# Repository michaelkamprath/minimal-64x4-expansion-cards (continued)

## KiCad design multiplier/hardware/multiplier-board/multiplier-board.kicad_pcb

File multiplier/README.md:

# Integer Multiplication Accelerator for the Minimal 64x4 Computer
This project enables hardware-accelerated multiplication on the [Minimal 64x4 Home Computer](https://github.com/slu4coder/Minimal-64x4-Home-Computer/), exploring how multiplication works at a fundamental level in both software and hardware, using the Minimal 64x4 homebrew computer as a real-world test platform. Starting with a classic shifted-add multiplication algorithm implemented entirely in assembly, the project demonstrates both the mechanics and performance limits of software-based multiplication on an 8-bit CPU.

To dramatically improve performance, a dedicated hardware multiplier card is designed and built using discrete 74-series logic. The board implements a fully combinational 8-bit × 8-bit multiplier with memory-mapped I/O, allowing the CPU to offload multiplication and receive a 16-bit result in just a few clock cycles. The design is then extended in software to support full 16-bit × 16-bit multiplication through careful carry management.

The impact of hardware acceleration is demonstrated using a Mandelbrot renderer, where thousands of multiplications per frame make performance differences immediately visible. By comparing software-only and hardware-accelerated runs on real hardware, the project shows how a simple, purpose-built coprocessor can transform computational performance on a retro-style system.

# Hardware Multiplier Design
The hardware multiplier is a memory-mapped expansion board for the Minimal 64x4 that implements an 8-bit × 8-bit unsigned multiplication entirely in combinational logic. The design uses a planar array of 74AHCT08 AND gates to generate all partial products, followed by a cascade of 74HCT283 4-bit adders to sum those partial products and propagate carries. Because the multiplier core is purely combinational, no clocking, state machine, or control logic is required; once valid operands are presented, the result settles after the inherent gate propagation delay.

Operands are latched from the system data bus using 74AHCT374 registers to isolate the combinational logic from the shared bus and to ensure stable inputs during computation. The 16-bit result is continuously driven internally and presented to the host system through 74AHCT245 bidirectional bus transceivers when the board is selected. Address decoding is handled using 74HCT688 magnitude comparators, with a small programmable logic device (ATF16V8) providing glue logic for timing, output enable control, and bus arbitration.

Worst-case propagation delay is dominated by carry propagation through the adder array and is approximately 160 ns, corresponding to roughly two CPU cycles on an 8 MHz Minimal 64x4. From the CPU’s perspective, multiplication is reduced to a small number of memory writes and reads, enabling a substantial performance improvement over the software-only shifted-add implementation.

```text
                     ┌─────────────────────────┐
                     │        CPU / BUS        │
                     │  Address • Data • Ctrl  │
                     └───────────┬─────────────┘
                                 │
                        Memory-Mapped I/O
                                 │
        ┌────────────────────────▼────────────────────────┐
        │            Hardware Multiplier Board            │
        │                                                 │
        │  ┌───────────────┐      ┌────────────────────┐  │
        │  │ Input Latch A │◄─────┤                    │  │
        │  │  (8-bit)      │      │                    │  │
        │  └───────────────┘      │                    │  │
        │                         │                    │  │
        │  ┌───────────────┐      │  Combinational     │  │
        │  │ Input Latch B │◄─────┤  Multiplier Core   │  │
        │  │  (8-bit)      │      │  (AND Plane +      │  │
        │  └───────────────┘      │   Adder Array)     │  │
        │                         │                    │  │
        │                         │                    │  │
        │                         └─────────┬──────────┘  │
        │                                   │             │
        │                          16-bit Result          │
        │                                   │             │
        │                    ┌──────────────▼────────────┐│
        │                    │  Output Bus Transceivers  ││
        │                    │       (16-bit)            ││
        │                    └──────────────┬────────────┘│
        │                                   │             │
        │  ┌──────────────────────────┐     │             │
        │  │ Address Decode & Control │◄────┘             │
        │  │ (Comparators + PLD)      │                   │
        │  └──────────────────────────┘                   │
        └─────────────────────────────────────────────────┘
```
The overall structure of the hardware multiplier is shown in the block diagram above. The board interfaces with the CPU exclusively through memory-mapped I/O on the shared system bus. Operand values are written by the CPU into two 8-bit input latches (Operand A and Operand B), which isolate the multiplier core from bus activity and continuously present stable inputs to the combinational logic.

At the center of the design is a purely combinational multiplier core composed of an AND-gate partial-product plane followed by an adder array that collapses those partial products into a 16-bit result. Because the core has no internal state, clocking, or control signals, the result is produced automatically as signals propagate through the logic once the operands are latched.

The 16-bit result is connected to the system data bus through output bus transceivers that are enabled only during valid read cycles. Address decoding and timing control logic ensure the board responds only within its assigned address range and never drives the bus outside of those cycles. From the CPU’s perspective, the hardware multiplier appears as a small set of deterministic, memory-mapped registers, with computation latency bounded solely by combinational propagation delay.

# Compiling the Software
All software found in the [software](./software/) directory is compiled with [BespokeASM](https://github.com/michaelkamprath/bespokeasm), which supports the Minimal 64x4. [Carsten Herting](https://github.com/slu4coder), the creator of the Minimal 64x4, also provides an assembler for it, but that assembler is quite minimal (by design). One key shortcoming is the inability to import library code into the current compilation. BespokeASM enables importing libraries and includes several other features that this project’s software depends on.

To compile the speech code in this repository, use the following command:

```sh
bespokeasm compile -c /path/to/bespokeasm/examples/slu4-minimal-64x4/slu4-minimal-64x4.yaml -n -p -t intel_hex -D USE_ACCELERATOR mandelbrot.min64x4
```
Where `/path/to/bespokeasm` is the path to the BespokeASM repository on your computer. You may remove the `-D USE_ACCELERATOR` if you wish to compile the program to use software-only multiplication.

This will produce an Intel HEX representation of the compiled program, which can then be sent to the Minimal 64x4 using its `receive` command.

# Video

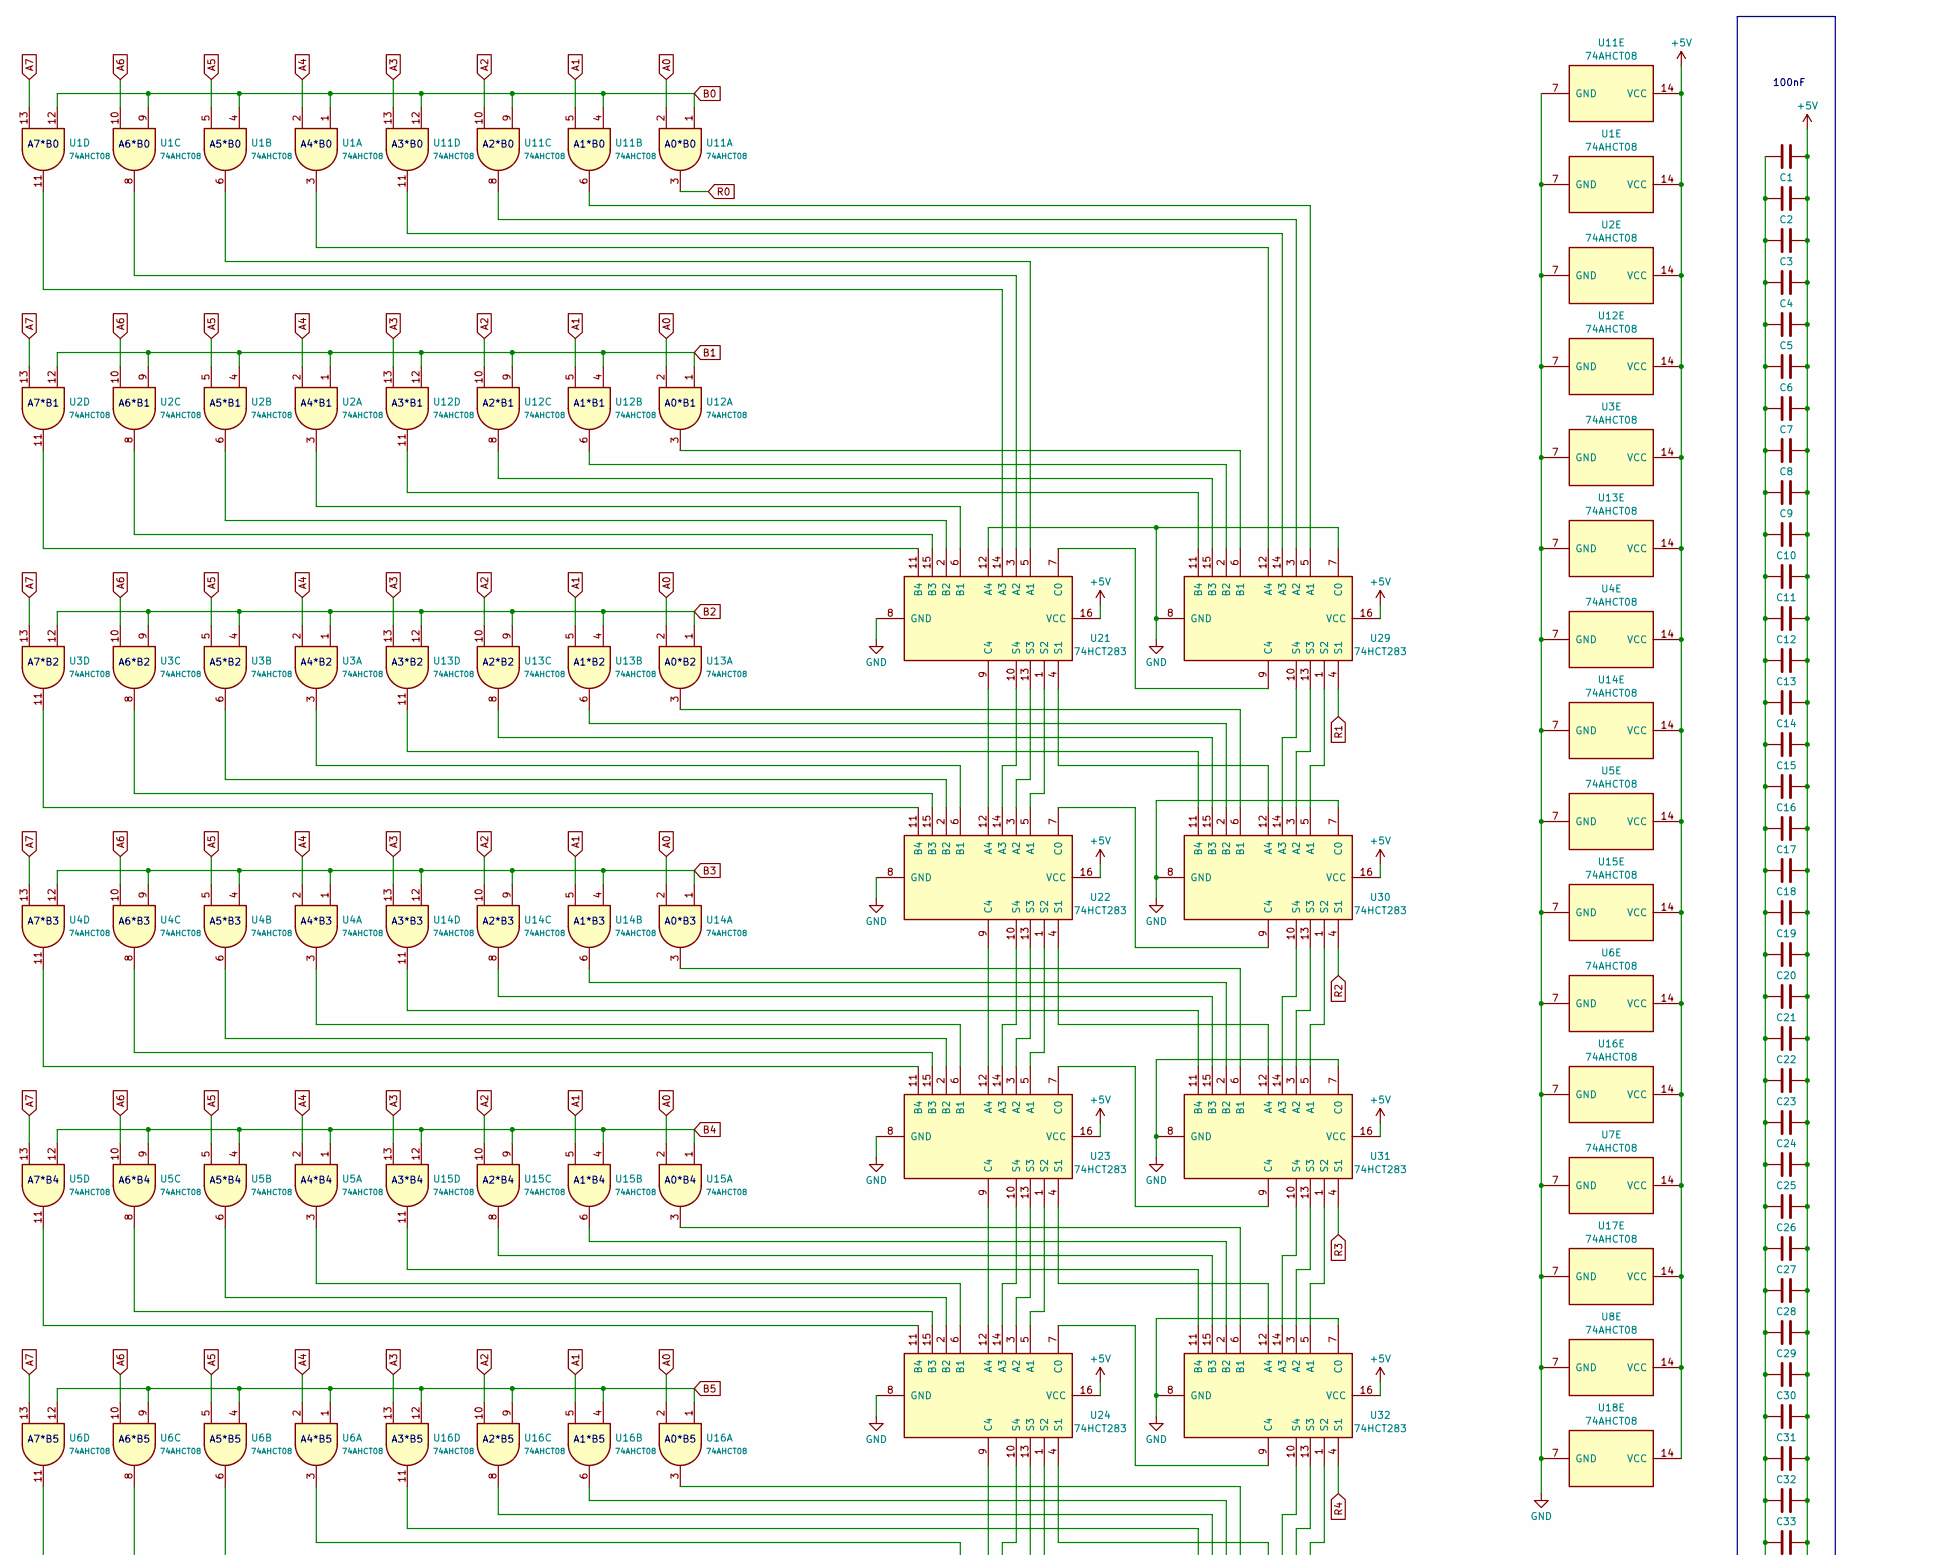
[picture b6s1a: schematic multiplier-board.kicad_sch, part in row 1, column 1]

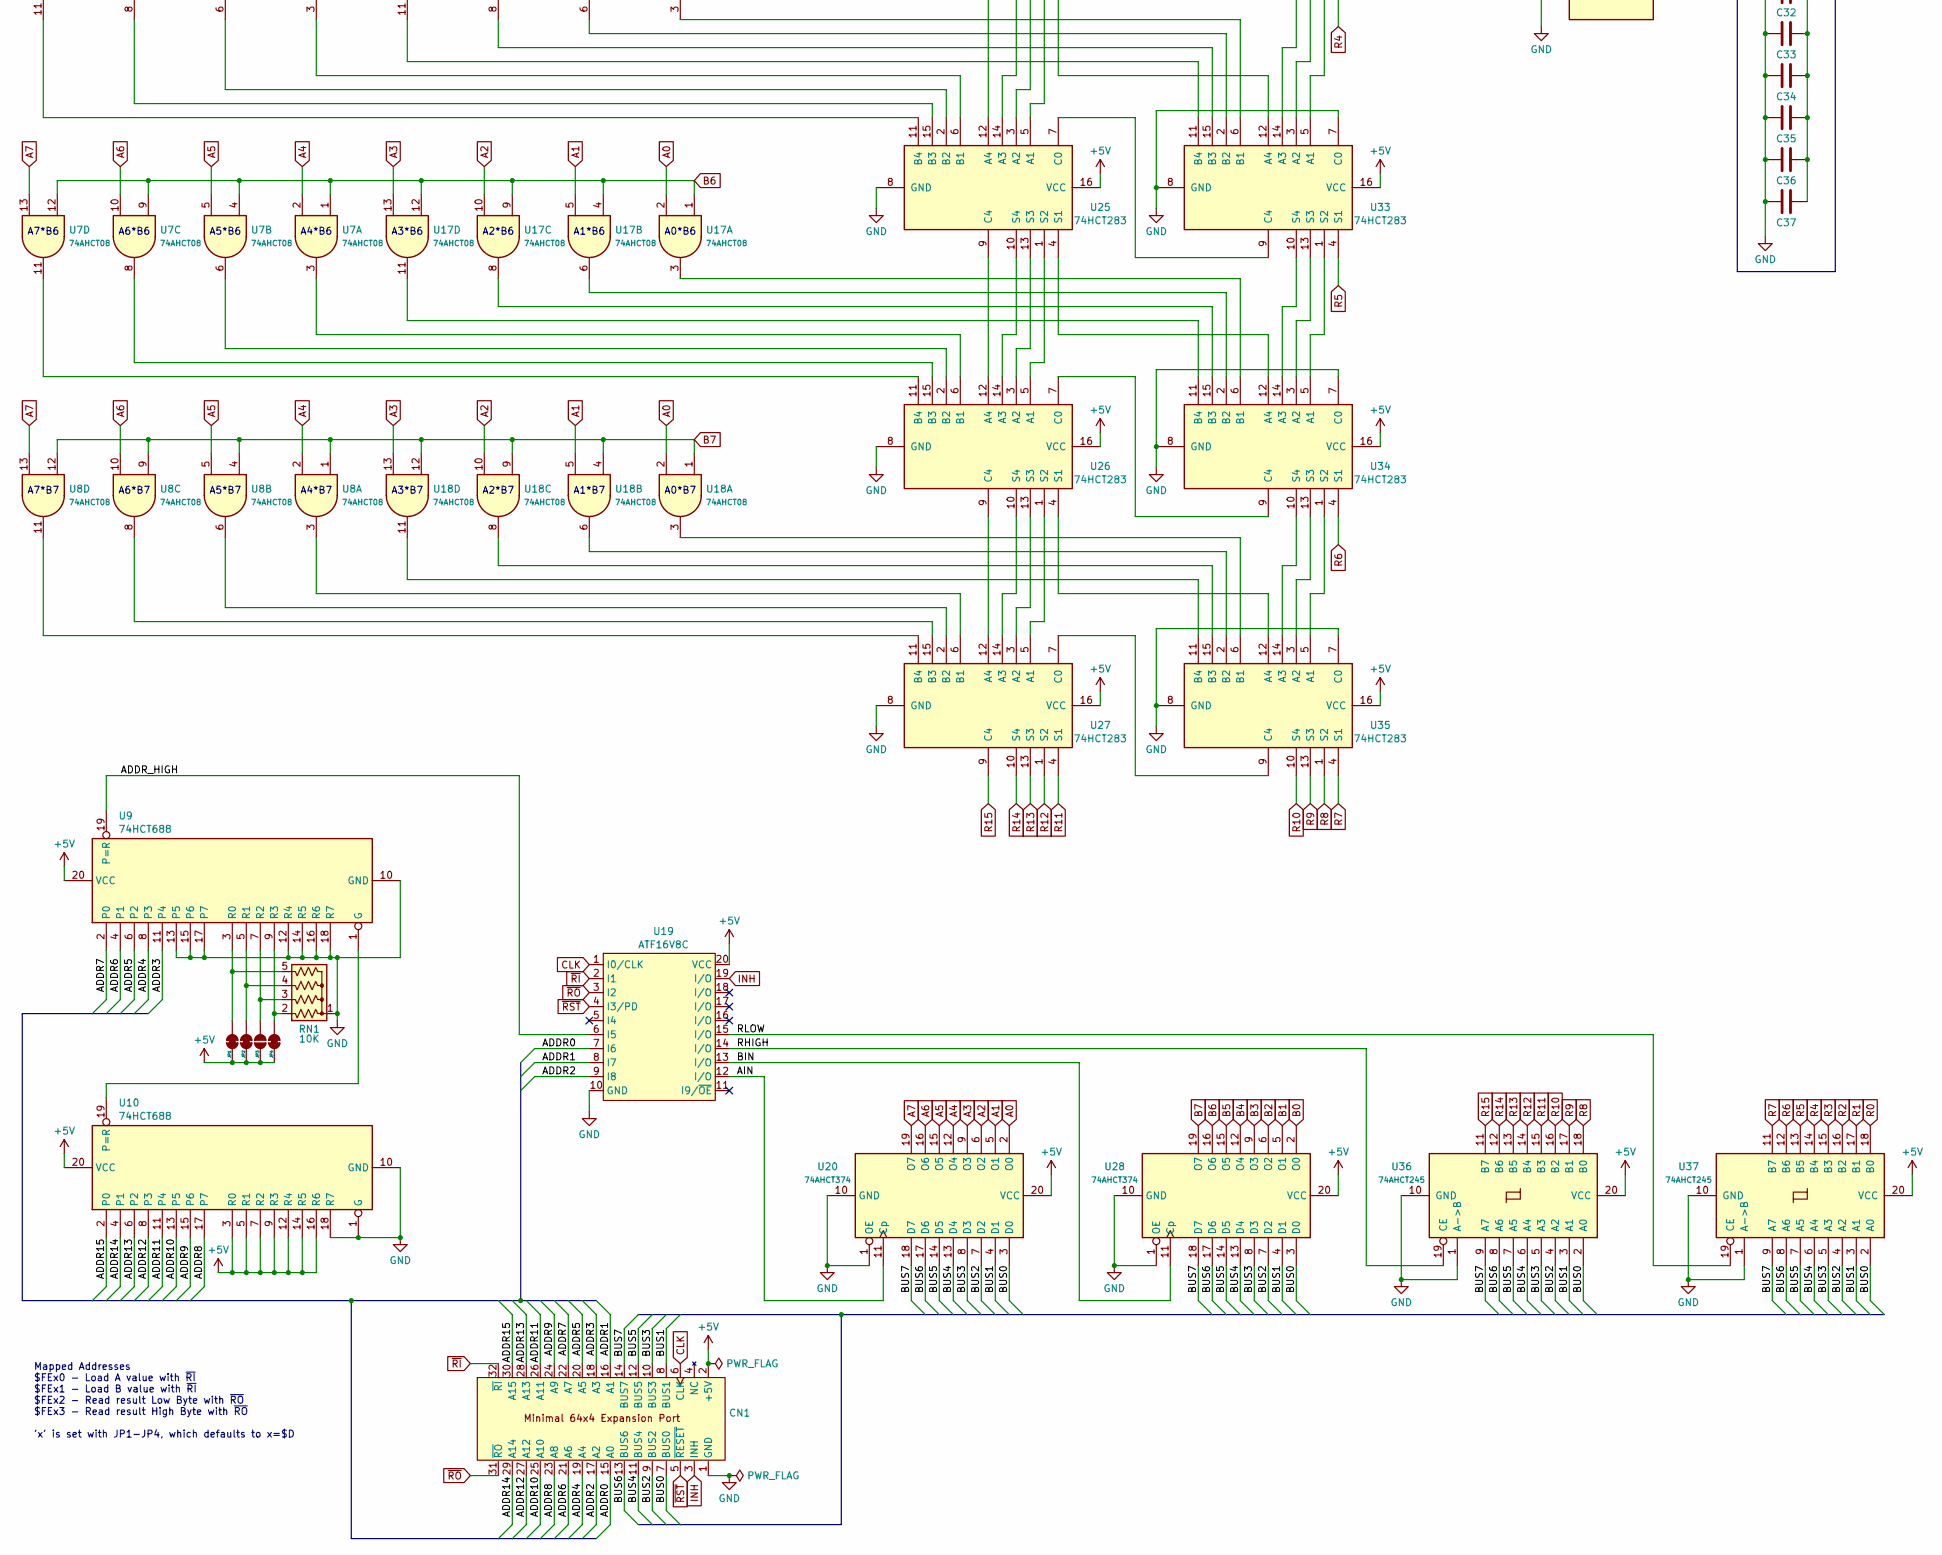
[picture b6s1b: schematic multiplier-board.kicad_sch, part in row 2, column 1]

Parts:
C1, C2, C3, C4, C5, C6, C7, C8, C9, C10, C11, C12, C13, C14, C15, C16, C17, C18, C19, C20, C21, C22, C23, C24, C25, C26, C27, C28, C29, C30, C31, C32, C33, C34, C35, C36, C37: 100 nF; C_0805_2012Metric_Pad1.18x1.45mm_HandSolder
CN1: PinHeader_2x16_P2.54mm_Horizontal
JP1, JP2, JP4: SolderJumper_2_Bridged; SolderJumper-2_P1.3mm_Bridged_RoundedPad1.0x1.5mm
JP3: SolderJumper_2_Open; SolderJumper-2_P1.3mm_Open_RoundedPad1.0x1.5mm
RN1: 10K; R_Array_SIP5
U1, U2, U3, U4, U5, U6, U7, U8, U11, U12, U13, U14, U15, U16, U17, U18: 74AHCT08; SOIC-14_3.9x8.7mm_P1.27mm
U9, U10: 74HCT688; SOIC-20W_7.5x12.8mm_P1.27mm
U19: ATF16V8C; DIP-20_W7.62mm_Socket
U20, U28: 74AHCT374; SOIC-20W_7.5x12.8mm_P1.27mm
U21, U22, U23, U24, U25, U26, U27, U29, U30, U31, U32, U33, U34, U35: 74HCT283; SOIC-16_3.9x9.9mm_P1.27mm
U36, U37: 74AHCT245; SOIC-20W_7.5x12.8mm_P1.27mm

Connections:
+5V: C1.2, C2.2, C3.2, C4.2, C5.2, C6.2, C7.2, C8.2, C9.2, C10.2, C11.2, C12.2, C13.2, C14.2, C15.2, C16.2, C17.2, C18.2, C19.2, C20.2, C21.2, C22.2, C23.2, C24.2, C25.2, C26.2, C27.2, C28.2, C29.2, C30.2, C31.2, C32.2, C33.2, C34.2, C35.2, C36.2, C37.2, CN1.2 (+5V), JP1.1 (A), JP2.1 (A), JP3.1 (A), JP4.1 (A), U1.14 (VCC), U2.14 (VCC), U3.14 (VCC), U4.14 (VCC), U5.14 (VCC), U6.14 (VCC), U7.14 (VCC), U8.14 (VCC), U9.20 (VCC), U10.3 (R0), U10.5 (R1), U10.7 (R2), U10.9 (R3), U10.12 (R4), U10.14 (R5), U10.16 (R6), U10.20 (VCC), U11.14 (VCC), U12.14 (VCC), U13.14 (VCC), U14.14 (VCC), U15.14 (VCC), U16.14 (VCC), U17.14 (VCC), U18.14 (VCC), U19.20 (VCC), U20.20 (VCC), U21.16 (VCC), U22.16 (VCC), U23.16 (VCC), U24.16 (VCC), U25.16 (VCC), U26.16 (VCC), U27.16 (VCC), U28.20 (VCC), U29.16 (VCC), U30.16 (VCC), U31.16 (VCC), U32.16 (VCC), U33.16 (VCC), U34.16 (VCC), U35.16 (VCC), U36.20 (VCC), U37.20 (VCC)
/ADDR0: CN1.15 (A0), U19.7 (I6)
/ADDR1: CN1.16 (A1), U19.8 (I7)
/ADDR2: CN1.17 (A2), U19.9 (I8)
/ADDR3: CN1.18 (A3), U9.11 (P4)
/ADDR4: CN1.19 (A4), U9.8 (P3)
/ADDR5: CN1.20 (A5), U9.6 (P2)
/ADDR6: CN1.21 (A6), U9.4 (P1)
/ADDR7: CN1.22 (A7), U9.2 (P0)
/ADDR8: CN1.23 (A8), U10.17 (P7)
/ADDR9: CN1.24 (A9), U10.15 (P6)
/ADDR10: CN1.25 (A10), U10.13 (P5)
/ADDR11: CN1.26 (A11), U10.11 (P4)
/ADDR12: CN1.27 (A12), U10.8 (P3)
/ADDR13: CN1.28 (A13), U10.6 (P2)
/ADDR14: CN1.29 (A14), U10.4 (P1)
/ADDR15: CN1.30 (A15), U10.2 (P0)
/ADDR_HIGH: U9.19 (P=R), U19.6 (I5)
/AIN: U19.12 (I/O), U20.11 (Cp)
/BIN: U19.13 (I/O), U28.11 (Cp)
/BUS0: CN1.7 (BUS0), U20.3 (D0), U28.3 (D0), U36.2 (A0), U37.2 (A0)
/BUS1: CN1.8 (BUS1), U20.4 (D1), U28.4 (D1), U36.3 (A1), U37.3 (A1)
/BUS2: CN1.9 (BUS2), U20.7 (D2), U28.7 (D2), U36.4 (A2), U37.4 (A2)
/BUS3: CN1.10 (BUS3), U20.8 (D3), U28.8 (D3), U36.5 (A3), U37.5 (A3)
/BUS4: CN1.11 (BUS4), U20.13 (D4), U28.13 (D4), U36.6 (A4), U37.6 (A4)
/BUS5: CN1.12 (BUS5), U20.14 (D5), U28.14 (D5), U36.7 (A5), U37.7 (A5)
/BUS6: CN1.13 (BUS6), U20.17 (D6), U28.17 (D6), U36.8 (A6), U37.8 (A6)
/BUS7: CN1.14 (BUS7), U20.18 (D7), U28.18 (D7), U36.9 (A7), U37.9 (A7)
/RHIGH: U19.14 (I/O), U36.19 (CE)
/RLOW: U19.15 (I/O), U37.19 (CE)
A0: U11.2, U12.2, U13.2, U14.2, U15.2, U16.2, U17.2, U18.2, U20.2 (O0)
A1: U11.5, U12.5, U13.5, U14.5, U15.5, U16.5, U17.5, U18.5, U20.5 (O1)
A2: U11.10, U12.10, U13.10, U14.10, U15.10, U16.10, U17.10, U18.10, U20.6 (O2)
A3: U11.13, U12.13, U13.13, U14.13, U15.13, U16.13, U17.13, U18.13, U20.9 (O3)
A4: U1.2, U2.2, U3.2, U4.2, U5.2, U6.2, U7.2, U8.2, U20.12 (O4)
A5: U1.5, U2.5, U3.5, U4.5, U5.5, U6.5, U7.5, U8.5, U20.15 (O5)
A6: U1.10, U2.10, U3.10, U4.10, U5.10, U6.10, U7.10, U8.10, U20.16 (O6)
A7: U1.13, U2.13, U3.13, U4.13, U5.13, U6.13, U7.13, U8.13, U20.19 (O7)
B0: U1.1, U1.4, U1.9, U1.12, U11.1, U11.4, U11.9, U11.12, U28.2 (O0)
B1: U2.1, U2.4, U2.9, U2.12, U12.1, U12.4, U12.9, U12.12, U28.5 (O1)
B2: U3.1, U3.4, U3.9, U3.12, U13.1, U13.4, U13.9, U13.12, U28.6 (O2)
B3: U4.1, U4.4, U4.9, U4.12, U14.1, U14.4, U14.9, U14.12, U28.9 (O3)
B4: U5.1, U5.4, U5.9, U5.12, U15.1, U15.4, U15.9, U15.12, U28.12 (O4)
B5: U6.1, U6.4, U6.9, U6.12, U16.1, U16.4, U16.9, U16.12, U28.15 (O5)
B6: U7.1, U7.4, U7.9, U7.12, U17.1, U17.4, U17.9, U17.12, U28.16 (O6)
B7: U8.1, U8.4, U8.9, U8.12, U18.1, U18.4, U18.9, U18.12, U28.19 (O7)
CLK: CN1.6 (CLK), U19.1 (I0/CLK)
GND: C1.1, C2.1, C3.1, C4.1, C5.1, C6.1, C7.1, C8.1, C9.1, C10.1, C11.1, C12.1, C13.1, C14.1, C15.1, C16.1, C17.1, C18.1, C19.1, C20.1, C21.1, C22.1, C23.1, C24.1, C25.1, C26.1, C27.1, C28.1, C29.1, C30.1, C31.1, C32.1, C33.1, C34.1, C35.1, C36.1, C37.1, CN1.1 (GND), RN1.1 (common), U1.7 (GND), U2.7 (GND), U3.7 (GND), U4.7 (GND), U5.7 (GND), U6.7 (GND), U7.7 (GND), U8.7 (GND), U9.10 (GND), U9.12 (R4), U9.13 (P5), U9.14 (R5), U9.15 (P6), U9.16 (R6), U9.17 (P7), U9.18 (R7), U10.1 (G), U10.10 (GND), U10.18 (R7), U11.7 (GND), U12.7 (GND), U13.7 (GND), U14.7 (GND), U15.7 (GND), U16.7 (GND), U17.7 (GND), U18.7 (GND), U19.10 (GND), U20.1 (OE), U20.10 (GND), U21.8 (GND), U21.12 (A4), U22.8 (GND), U23.8 (GND), U24.8 (GND), U25.8 (GND), U26.8 (GND), U27.8 (GND), U28.1 (OE), U28.10 (GND), U29.7 (C0), U29.8 (GND), U30.7 (C0), U30.8 (GND), U31.7 (C0), U31.8 (GND), U32.7 (C0), U32.8 (GND), U33.7 (C0), U33.8 (GND), U34.7 (C0), U34.8 (GND), U35.7 (C0), U35.8 (GND), U36.1 (A->B), U36.10 (GND), U37.1 (A->B), U37.10 (GND)
INH: CN1.3 (INH), U19.19 (I/O)
unnamed: JP1.2 (B), RN1.5 (R4), U9.3 (R0)
unnamed: JP2.2 (B), RN1.4 (R3), U9.5 (R1)
unnamed: JP3.2 (B), RN1.3 (R2), U9.7 (R2)
unnamed: JP4.2 (B), RN1.2 (R1), U9.9 (R3)
unnamed: U9.1 (G), U10.19 (P=R)
unnamed: U1.6, U21.5 (A1)
unnamed: U1.8, U21.3 (A2)
unnamed: U1.11, U21.14 (A3)
unnamed: U2.3, U21.6 (B1)
unnamed: U2.6, U21.2 (B2)
unnamed: U2.8, U21.15 (B3)
unnamed: U2.11, U21.11 (B4)
unnamed: U21.7 (C0), U29.9 (C4)
unnamed: U21.9 (C4), U22.12 (A4)
unnamed: U21.4 (S1), U30.12 (A4)
unnamed: U21.1 (S2), U22.5 (A1)
unnamed: U21.13 (S3), U22.3 (A2)
unnamed: U21.10 (S4), U22.14 (A3)
unnamed: U3.3, U22.6 (B1)
unnamed: U3.6, U22.2 (B2)
unnamed: U3.8, U22.15 (B3)
unnamed: U3.11, U22.11 (B4)
unnamed: U22.7 (C0), U30.9 (C4)
unnamed: U22.9 (C4), U23.12 (A4)
unnamed: U22.4 (S1), U31.12 (A4)
unnamed: U22.1 (S2), U23.5 (A1)
unnamed: U22.13 (S3), U23.3 (A2)
unnamed: U22.10 (S4), U23.14 (A3)
unnamed: U4.3, U23.6 (B1)
unnamed: U4.6, U23.2 (B2)
unnamed: U4.8, U23.15 (B3)
unnamed: U4.11, U23.11 (B4)
unnamed: U23.7 (C0), U31.9 (C4)
unnamed: U23.9 (C4), U24.12 (A4)
unnamed: U23.4 (S1), U32.12 (A4)
unnamed: U23.1 (S2), U24.5 (A1)
unnamed: U23.13 (S3), U24.3 (A2)
unnamed: U23.10 (S4), U24.14 (A3)
unnamed: U5.3, U24.6 (B1)
unnamed: U5.6, U24.2 (B2)
unnamed: U5.8, U24.15 (B3)
unnamed: U5.11, U24.11 (B4)
unnamed: U24.7 (C0), U32.9 (C4)
unnamed: U24.9 (C4), U25.12 (A4)
unnamed: U24.4 (S1), U33.12 (A4)
unnamed: U24.1 (S2), U25.5 (A1)
unnamed: U24.13 (S3), U25.3 (A2)
unnamed: U24.10 (S4), U25.14 (A3)
unnamed: U6.3, U25.6 (B1)
unnamed: U6.6, U25.2 (B2)
unnamed: U6.8, U25.15 (B3)
unnamed: U6.11, U25.11 (B4)
unnamed: U25.7 (C0), U33.9 (C4)
unnamed: U25.9 (C4), U26.12 (A4)
unnamed: U25.4 (S1), U34.12 (A4)
unnamed: U25.1 (S2), U26.5 (A1)
unnamed: U25.13 (S3), U26.3 (A2)
unnamed: U25.10 (S4), U26.14 (A3)
unnamed: U7.3, U26.6 (B1)
unnamed: U7.6, U26.2 (B2)
unnamed: U7.8, U26.15 (B3)
unnamed: U7.11, U26.11 (B4)
unnamed: U26.7 (C0), U34.9 (C4)
unnamed: U26.9 (C4), U27.12 (A4)
unnamed: U26.4 (S1), U35.12 (A4)
unnamed: U26.1 (S2), U27.5 (A1)
unnamed: U26.13 (S3), U27.3 (A2)
unnamed: U26.10 (S4), U27.14 (A3)
unnamed: U8.3, U27.6 (B1)
unnamed: U8.6, U27.2 (B2)
unnamed: U8.8, U27.15 (B3)
unnamed: U8.11, U27.11 (B4)
unnamed: U27.7 (C0), U35.9 (C4)
unnamed: U11.6, U29.5 (A1)
unnamed: U11.8, U29.3 (A2)
unnamed: U11.11, U29.14 (A3)
unnamed: U1.3, U29.12 (A4)
unnamed: U12.3, U29.6 (B1)
unnamed: U12.6, U29.2 (B2)
unnamed: U12.8, U29.15 (B3)
unnamed: U12.11, U29.11 (B4)
unnamed: U29.1 (S2), U30.5 (A1)
unnamed: U29.13 (S3), U30.3 (A2)
unnamed: U29.10 (S4), U30.14 (A3)
unnamed: U13.3, U30.6 (B1)
unnamed: U13.6, U30.2 (B2)
unnamed: U13.8, U30.15 (B3)
unnamed: U13.11, U30.11 (B4)
unnamed: U30.1 (S2), U31.5 (A1)
unnamed: U30.13 (S3), U31.3 (A2)
unnamed: U30.10 (S4), U31.14 (A3)
unnamed: U14.3, U31.6 (B1)
unnamed: U14.6, U31.2 (B2)
unnamed: U14.8, U31.15 (B3)
unnamed: U14.11, U31.11 (B4)
unnamed: U31.1 (S2), U32.5 (A1)
unnamed: U31.13 (S3), U32.3 (A2)
unnamed: U31.10 (S4), U32.14 (A3)
unnamed: U15.3, U32.6 (B1)
unnamed: U15.6, U32.2 (B2)
unnamed: U15.8, U32.15 (B3)
unnamed: U15.11, U32.11 (B4)
unnamed: U32.1 (S2), U33.5 (A1)
unnamed: U32.13 (S3), U33.3 (A2)
unnamed: U32.10 (S4), U33.14 (A3)
unnamed: U16.3, U33.6 (B1)
unnamed: U16.6, U33.2 (B2)
unnamed: U16.8, U33.15 (B3)
unnamed: U16.11, U33.11 (B4)
unnamed: U33.1 (S2), U34.5 (A1)
unnamed: U33.13 (S3), U34.3 (A2)
unnamed: U33.10 (S4), U34.14 (A3)
unnamed: U17.3, U34.6 (B1)
unnamed: U17.6, U34.2 (B2)
unnamed: U17.8, U34.15 (B3)
unnamed: U17.11, U34.11 (B4)
unnamed: U34.1 (S2), U35.5 (A1)
unnamed: U34.13 (S3), U35.3 (A2)
unnamed: U34.10 (S4), U35.14 (A3)
unnamed: U18.3, U35.6 (B1)
unnamed: U18.6, U35.2 (B2)
unnamed: U18.8, U35.15 (B3)
unnamed: U18.11, U35.11 (B4)
R0: U11.3, U37.18 (B0)
R1: U29.4 (S1), U37.17 (B1)
R2: U30.4 (S1), U37.16 (B2)
R3: U31.4 (S1), U37.15 (B3)
R4: U32.4 (S1), U37.14 (B4)
R5: U33.4 (S1), U37.13 (B5)
R6: U34.4 (S1), U37.12 (B6)
R7: U35.4 (S1), U37.11 (B7)
R8: U35.1 (S2), U36.18 (B0)
R9: U35.13 (S3), U36.17 (B1)
R10: U35.10 (S4), U36.16 (B2)
R11: U27.4 (S1), U36.15 (B3)
R12: U27.1 (S2), U36.14 (B4)
R13: U27.13 (S3), U36.13 (B5)
R14: U27.10 (S4), U36.12 (B6)
R15: U27.9 (C4), U36.11 (B7)
~RI: CN1.32 (~RI), U19.2 (I1)
~RO: CN1.31 (~RO), U19.3 (I2)
~RST: CN1.5 (~RESET), U19.4 (I3/PD)

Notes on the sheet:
A5*B6
A6*B7
A5*B1
A2*B4
A1*B3
A1*B5
A2*B5
A1*B2
A3*B2
A2*B1
A2*B0
A2*B6
A4*B1
A4*B0
A0*B3
A6*B3
A4*B3
A7*B6
A0*B0
A2*B7
A5*B5
A7*B4
A7*B0
A4*B6
A6*B4
A3*B6
A3*B5
A7*B3
A2*B2
A4*B2
A1*B4
A3*B0
A5*B0
A5*B7
A1*B6
A0*B7
A4*B7
Mapped Addresses $FEx0 - Load A value with ~{RI} $FEx1 - Load B value with ~{RI} $FEx2 - Read result Low Byte with ~{RO} $FEx3 - Read result High Byte with ~{RO} 'x' is set with JP1-JP4, which defaults to x=$D
A0*B2
A6*B2

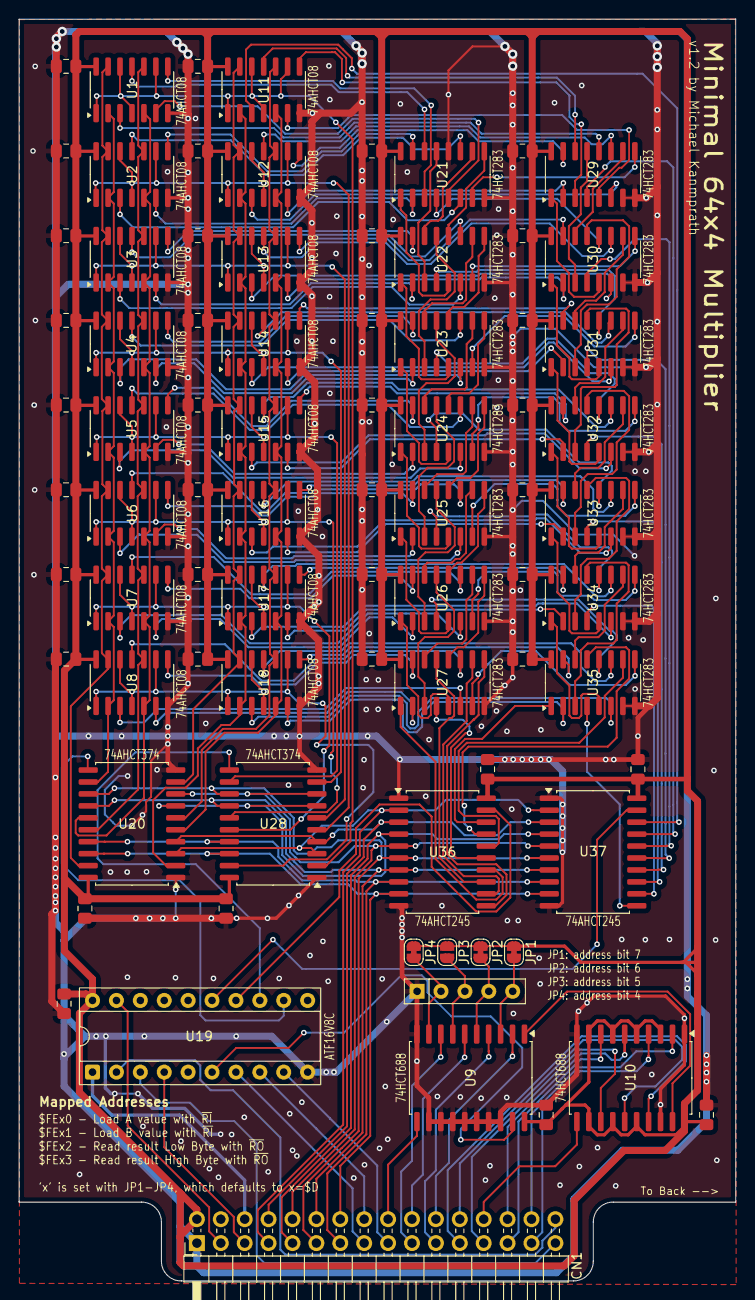
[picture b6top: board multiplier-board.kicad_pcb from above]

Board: 2 copper layers, 76.2 x 134.1 mm, 80 parts (0 on the bottom side), 191 nets.

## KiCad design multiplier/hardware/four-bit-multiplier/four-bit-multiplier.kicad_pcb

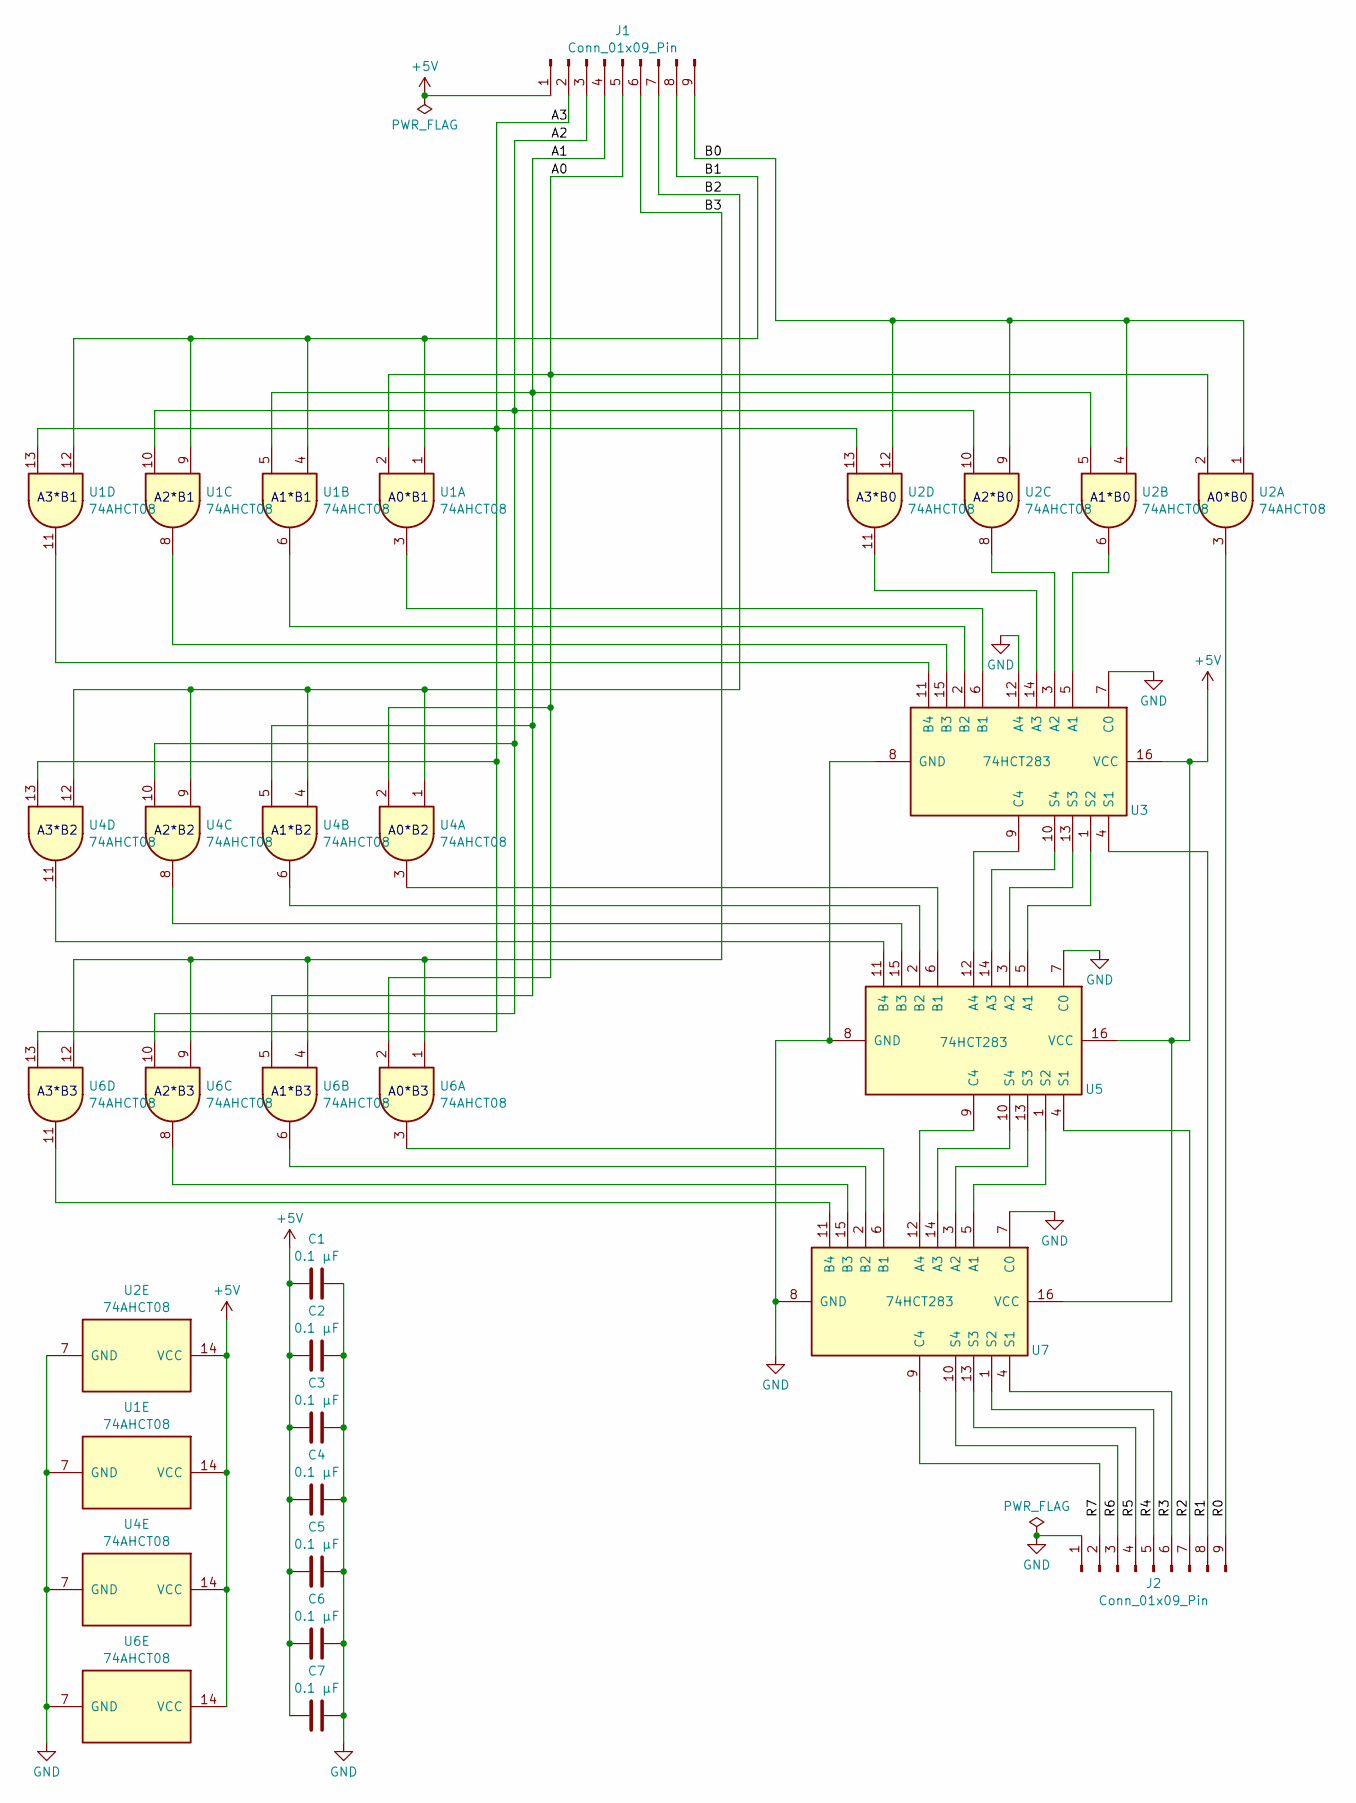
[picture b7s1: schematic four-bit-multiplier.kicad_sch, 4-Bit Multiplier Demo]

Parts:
C1, C2, C3, C4, C5, C6, C7: 0.1 µF; C_0805_2012Metric_Pad1.18x1.45mm_HandSolder
J1, J2: Conn_01x09_Pin; PinHeader_1x09_P2.54mm_Vertical
U1, U2, U4, U6: 74AHCT08; SOIC-14_3.9x8.7mm_P1.27mm
U3, U5, U7: 74HCT283; SOIC-16_3.9x9.9mm_P1.27mm

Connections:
+5V: C1.1, C2.1, C3.1, C4.1, C5.1, C6.1, C7.1, J1.1, U1.14 (VCC), U2.14 (VCC), U3.16 (VCC), U4.14 (VCC), U5.16 (VCC), U6.14 (VCC), U7.16 (VCC)
/A0: J1.5, U1.2, U2.2, U4.2, U6.2
/A1: J1.4, U1.5, U2.5, U4.5, U6.5
/A2: J1.3, U1.10, U2.10, U4.10, U6.10
/A3: J1.2, U1.13, U2.13, U4.13, U6.13
/B0: J1.9, U2.1, U2.4, U2.9, U2.12
/B1: J1.8, U1.1, U1.4, U1.9, U1.12
/B2: J1.7, U4.1, U4.4, U4.9, U4.12
/B3: J1.6, U6.1, U6.4, U6.9, U6.12
/R0: J2.9, U2.3
/R1: J2.8, U3.4 (S1)
/R2: J2.7, U5.4 (S1)
/R3: J2.6, U7.4 (S1)
/R4: J2.5, U7.1 (S2)
/R5: J2.4, U7.13 (S3)
/R6: J2.3, U7.10 (S4)
/R7: J2.2, U7.9 (C4)
GND: C1.2, C2.2, C3.2, C4.2, C5.2, C6.2, C7.2, J2.1, U1.7 (GND), U2.7 (GND), U3.7 (C0), U3.8 (GND), U3.12 (A4), U4.7 (GND), U5.7 (C0), U5.8 (GND), U6.7 (GND), U7.7 (C0), U7.8 (GND)
unnamed: U2.6, U3.5 (A1)
unnamed: U2.8, U3.3 (A2)
unnamed: U2.11, U3.14 (A3)
unnamed: U1.3, U3.6 (B1)
unnamed: U1.6, U3.2 (B2)
unnamed: U1.8, U3.15 (B3)
unnamed: U1.11, U3.11 (B4)
unnamed: U3.9 (C4), U5.12 (A4)
unnamed: U3.1 (S2), U5.5 (A1)
unnamed: U3.13 (S3), U5.3 (A2)
unnamed: U3.10 (S4), U5.14 (A3)
unnamed: U4.3, U5.6 (B1)
unnamed: U4.6, U5.2 (B2)
unnamed: U4.8, U5.15 (B3)
unnamed: U4.11, U5.11 (B4)
unnamed: U5.9 (C4), U7.12 (A4)
unnamed: U5.1 (S2), U7.5 (A1)
unnamed: U5.13 (S3), U7.3 (A2)
unnamed: U5.10 (S4), U7.14 (A3)
unnamed: U6.3, U7.6 (B1)
unnamed: U6.6, U7.2 (B2)
unnamed: U6.8, U7.15 (B3)
unnamed: U6.11, U7.11 (B4)

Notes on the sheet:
A3*B3
A1*B2
A1*B0
A0*B0
A2*B2
A2*B1
A1*B1
A1*B3
A2*B0
A3*B2
A2*B3
A0*B3
A3*B1
A3*B0
A0*B2
A0*B1

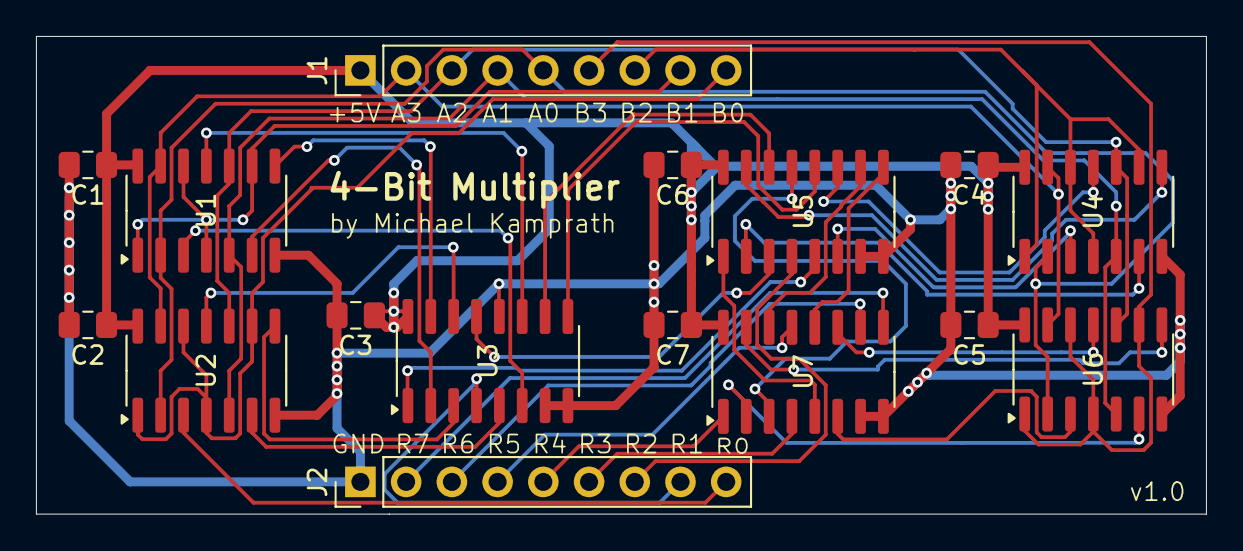
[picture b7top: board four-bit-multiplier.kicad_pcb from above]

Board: 2 copper layers, 65.0 x 26.5 mm, 16 parts (0 on the bottom side), 41 nets.

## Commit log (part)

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2024-12-25 added backplane
2024-12-25 speech synthizer setup
2024-12-25 updatedd PCB layouts
2024-12-25 added expansion connector
2024-12-25 tweaked timings
2024-12-25 updated documentation
2024-12-25 added sample code for speech
2024-12-25 created speech pcb
2024-12-25 update speech pld file and more
2024-12-25 first bespokeasm compilable version of invaders
2024-12-25 updated sounds
2024-12-25 improved output format
2024-12-25 improved sounds for speech invaders
2024-12-25 added speech samples
2024-12-25 added lpc player app
2024-12-25 improved backplane
2024-12-25 removed barier mosfet
2024-12-25 added pull down resistors
2024-12-25 tweaks
2024-12-25 typo
2024-12-25 added datasheets
2024-12-29 added is_talking subroutine
2024-12-29 improved silkscreen
2024-12-29 added pull down resistor
2024-12-31 improved documentation
2025-01-01 added BOM
2025-01-04 updated timing
2025-04-11 update kicad version
2025-05-30 tweaked output display
2025-07-04 added wotw speech demo
2025-07-04 first schematice of 4-bit multiplier
2025-07-04 fixed carry
2025-07-26 added .gitignore
2025-08-18 first version of multiplier board
2025-08-18 corrected part designator
2025-08-25 start of software for multiplier board
2025-08-26 added signed integer multiplications
2025-08-27 got mandelbrot working
2025-08-27 improved performance of multiply_i16
2025-08-28 improved performance
2025-08-28 added controller PLD
2025-08-28 linting
2025-08-31 corrected issues
2025-08-31 corrected an error
2025-09-01 added better ground plane
2025-09-02 updated version
2025-09-07 various improvements
2025-09-07 changed pcb to 4-layer with internal ground planes
2025-09-10 improved formatting
2025-09-15 updated syntax for updated bespokeasm
2025-10-07 updated for new bespokeasm
2025-11-28 rotating rectangle demo
2025-11-29 improved rotating rect app
2025-12-14 reverted PLD
2025-12-24 fixed bug
2025-12-24 fixed multiple definitions
2025-12-24 speed improvement
2025-12-24 minor improvements
2026-01-17 improved signal line isolation
2026-01-18 improved signal integrity
2026-01-24 Hardware Multiplier (#1)
    Created a hardware multiplier for the Minimal 64x4
2026-01-29 improvements
2026-01-31 fixed bug with signed right shift
2026-02-02 added Karastuba algorithm demo
2026-02-02 require USE_ACCELERATOR defined
2026-02-02 Karatsuba Demo (#2)
    Added demo and tests of using the Karastuba algorithm to speed up multiplication, even with the hardware multiplier card.
2026-02-03 corrected calculation bug
2026-02-03 added check to ensure test is configured correctly
2026-02-03 refactored and created mathlib64
2026-02-03 Further work on Karastuba implementation (#3)
    Created mathlib64.min64x4 to implement multiplication based on Karastuba algorithm. Also added some tests to ensure algorithm correctness.
2026-02-03 removed redundant compiler message
2026-02-03 added language documentation for AI agent
2026-02-03 typos
2026-02-03 gitignore
2026-02-16 card schematic completed
2026-02-17 timer pcb layout
2026-02-22 created consolidated mathlib
2026-02-22 improved documentation and other fixes
2026-02-28 layout improvements
2026-02-28 corrected design flaw in hardware
2026-03-07 improved karatsuba demo
2026-03-07 improved docs
2026-03-07 Timer Card (#4)
    Adds a clock counting Timer Card.
2026-04-05 improved timer card design
2026-04-20 added Extended Min versions of speech card demos
2026-04-26 reformatted
2026-04-27 updated syntax for xmin v0.5
2026-04-28 xmin speech demos
2026-04-28 small correction
2026-04-30 small tweaks
2026-05-02 improved timer pld
